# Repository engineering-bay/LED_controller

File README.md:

# LED_controller
Светодиодный драйвер

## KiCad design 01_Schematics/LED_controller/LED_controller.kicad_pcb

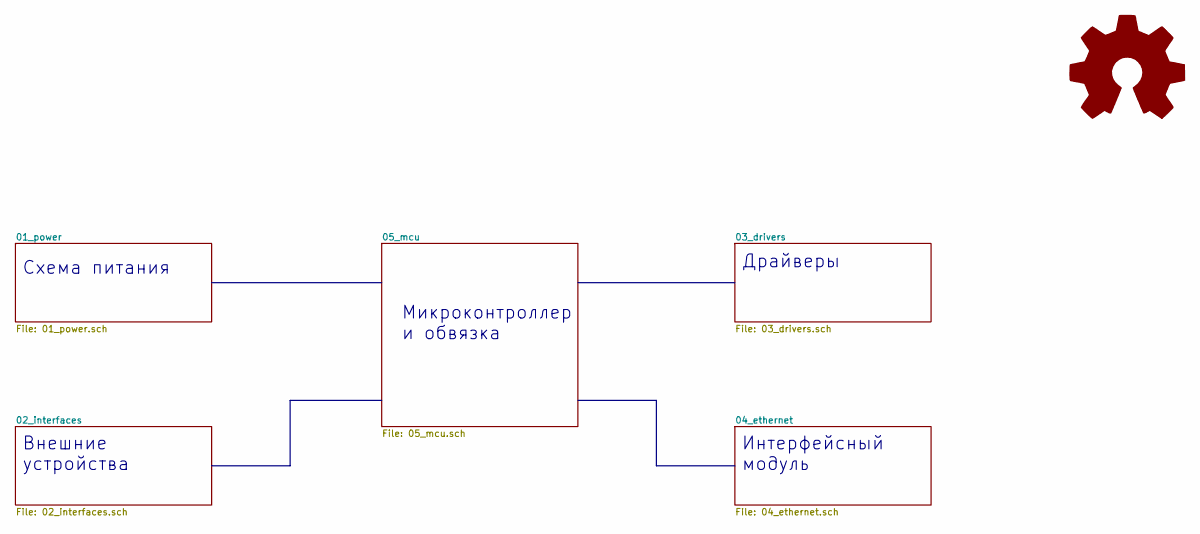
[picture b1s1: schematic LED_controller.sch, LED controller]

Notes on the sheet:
Схема питания
Микроконтроллер и обвязка
Внешние устройства
Интерфейсный модуль
Драйверы

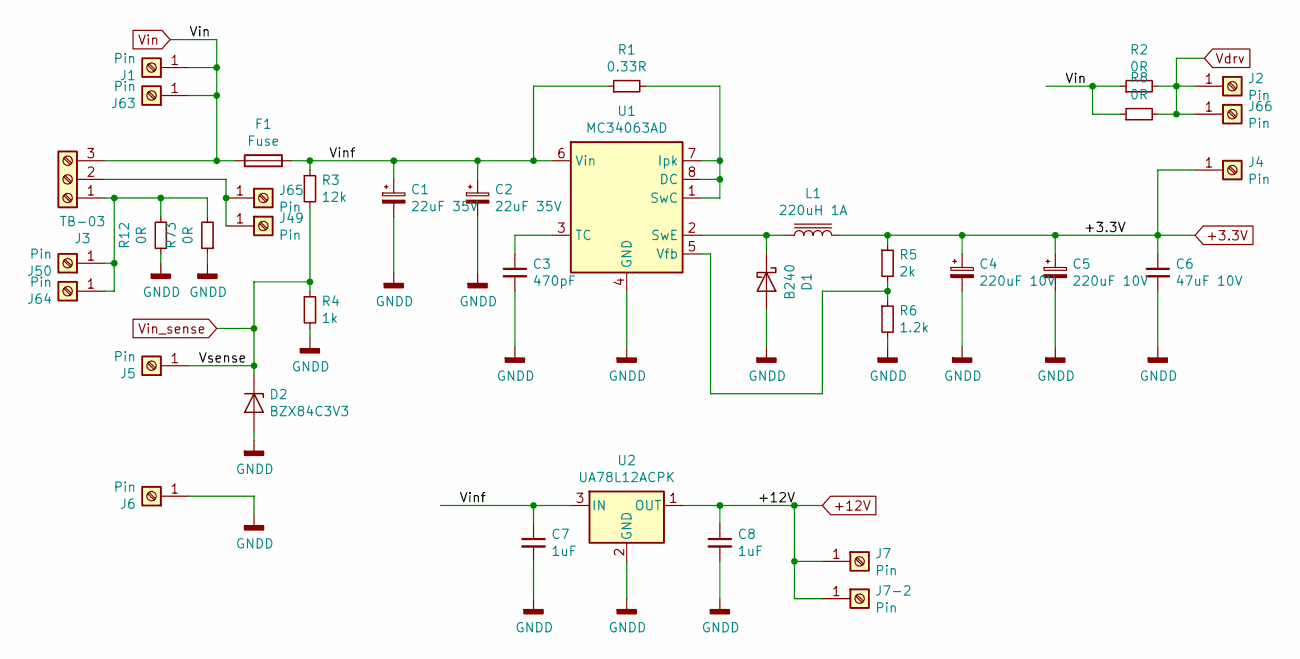
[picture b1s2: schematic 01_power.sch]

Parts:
C1, C2: 22uF 35V; CP_EIA-7343-31_Kemet-D_Pad2.25x2.55mm_HandSolder; partnum 293D226X9035D2TE3
C3: 470pF; C_0805_2012Metric_Pad1.15x1.40mm_HandSolder; partnum CC0805JRNPO9BN471
C4, C5: 220uF 10V; CP_EIA-7343-31_Kemet-D_Pad2.25x2.55mm_HandSolder; partnum 293D227X9010D2TE3
C6: 47uF 10V; C_1206_3216Metric_Pad1.42x1.75mm_HandSolder; partnum GRM31CR61A476ME15L
C7, C8: 1uF; C_0805_2012Metric_Pad1.15x1.40mm_HandSolder; partnum CC0805KKX7R9BB105
D1: B240; D_SMB
D2: BZX84C3V3; D_SOT-23_ANK
F1: Fuse; MF-R185; partnum MF-R090
J1, J2, J4, J5, J6, J7, J7-2, J49, J50, J63, J64, J65, J66: Pin; TestPoint_THTPad_2.0x2.0mm_Drill1.0mm
J3: TB-03; TB-03_metric; partnum TB-03
L1: 220uH 1A; SRR1208; partnum SRR1208-221KL
R1: 0.33R; R_0805_2012Metric_Pad1.15x1.40mm_HandSolder; partnum RL0805FR-070R33L
R2, R8, R12, R73: 0R; R_0805_2012Metric_Pad1.15x1.40mm_HandSolder; partnum RC2010JK-070RL
R3: 12k; R_0805_2012Metric_Pad1.15x1.40mm_HandSolder; partnum RC0805FR-0712KL
R4: 1k; R_0805_2012Metric_Pad1.15x1.40mm_HandSolder; partnum RC0805FR-071KL
R5: 2k; R_0805_2012Metric_Pad1.15x1.40mm_HandSolder; partnum RC0805FR-072KL
R6: 1.2k; R_0805_2012Metric_Pad1.15x1.40mm_HandSolder; partnum RC0805FR-071K2L
U1: MC34063AD; SOIC-8_3.9x4.9mm_P1.27mm
U2: UA78L12ACPK; SOT-89-3; partnum UA78L12ACPK

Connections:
+3.3V: C4.1, C5.1, C6.1, J4.1, L1.2, R5.1; also elsewhere on the board
+12V: C8.1, J7.1, J7-2.1, U2.1 (OUT); also elsewhere on the board
/01_power/Vinf: C1.1, C2.1, C7.1, F1.2, R1.1, R3.1, U1.6 (Vin), U2.3 (IN)
GND: C1.2, C2.2, C3.2, C4.2, C5.2, C6.2, C7.2, C8.2, D1.2 (A), D2.2 (A), J6.1, R4.2, R6.2, R12.1, R73.1, U1.4 (GND), U2.2 (GND); also elsewhere on the board
unnamed: C3.1, U1.3 (TC)
unnamed: D1.1 (K), L1.1, U1.2 (SwE)
unnamed: J3.1, J50.1, J64.1, R12.2, R73.2
unnamed: J3.2, J49.1, J65.1
unnamed: R1.2, U1.1 (SwC), U1.7 (Ipk), U1.8 (DC)
unnamed: R5.2, R6.1, U1.5 (Vfb)
Vdrv: J2.1, J66.1, R2.2, R8.2; also elsewhere on the board
Vin: F1.1, J1.1, J3.3, J63.1, R2.1, R8.1
Vin_sense: D2.1 (K), J5.1, R3.2, R4.1; also elsewhere on the board

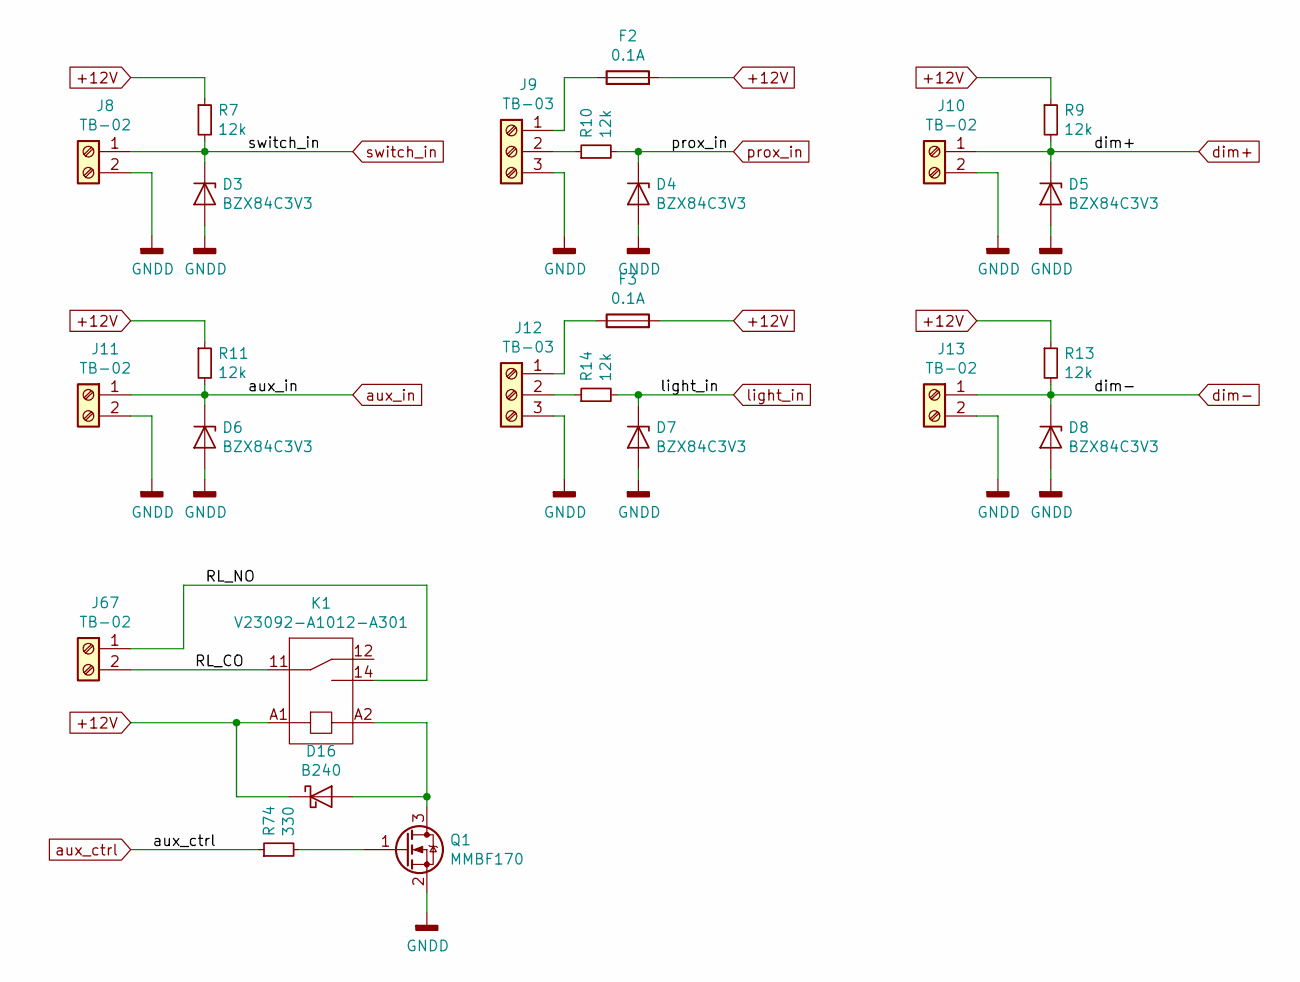
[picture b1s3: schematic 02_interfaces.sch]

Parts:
D3, D4, D5, D6, D7, D8: BZX84C3V3; D_SOT-23_ANK
D16: B240; D_SMB
F2, F3: 0.1A; R_1812_4532Metric_Pad1.30x3.40mm_HandSolder; partnum MF-MSMF010
J8, J10, J11, J13, J67: TB-02; TB-02_metric; partnum 300-021-12
J9, J12: TB-03; TB-03_metric; partnum 300-031-12
K1: V23092-A1012-A301; Relay_TE_V23092
Q1: MMBF170; SOT-23
R7, R9, R10, R11, R13, R14: 12k; R_0805_2012Metric_Pad1.15x1.40mm_HandSolder; partnum RC0805FR-0712KL
R74: 330; R_0805_2012Metric_Pad1.15x1.40mm_HandSolder; partnum RC0805FR-07330RL

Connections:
+12V: D16.1 (K), F2.2, F3.2, K1.A1, R7.1, R9.1, R11.1, R13.1; also elsewhere on the board
/02_interfaces/RL_CO: J67.2, K1.11
/02_interfaces/RL_NO: J67.1, K1.14
GND: D3.2 (A), D4.2 (A), D5.2 (A), D6.2 (A), D7.2 (A), D8.2 (A), J8.2, J9.3, J10.2, J11.2, J12.3, J13.2, Q1.2 (S); also elsewhere on the board
unnamed: D16.2 (A), K1.A2, Q1.3 (D)
unnamed: F2.1, J9.1
unnamed: F3.1, J12.1
unnamed: J9.2, R10.1
unnamed: J12.2, R14.1
unnamed: Q1.1 (G), R74.2
aux_ctrl: R74.1; also elsewhere on the board
aux_in: D6.1 (K), J11.1, R11.2; also elsewhere on the board
dim+: D5.1 (K), J10.1, R9.2; also elsewhere on the board
dim-: D8.1 (K), J13.1, R13.2; also elsewhere on the board
light_in: D7.1 (K), R14.2; also elsewhere on the board
prox_in: D4.1 (K), R10.2; also elsewhere on the board
switch_in: D3.1 (K), J8.1, R7.2; also elsewhere on the board

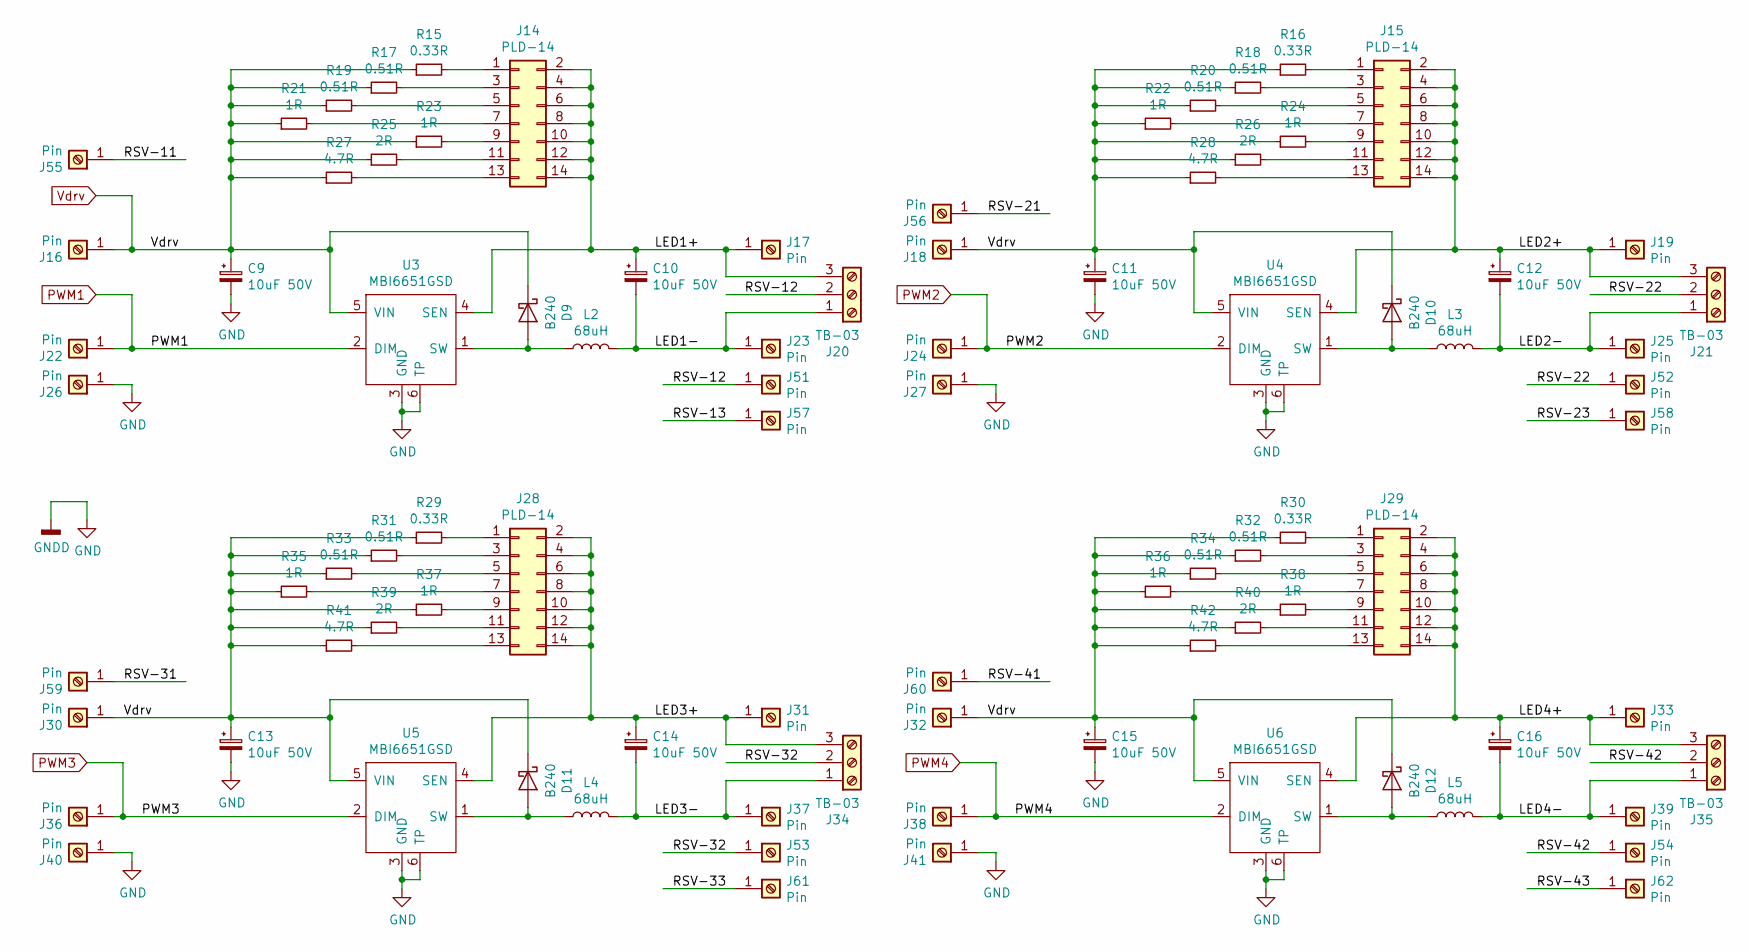
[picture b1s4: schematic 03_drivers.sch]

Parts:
C9, C10, C11, C12, C13, C14, C15, C16: 10uF 50V; CP_EIA-7343-31_Kemet-D_Pad2.25x2.55mm_HandSolder; partnum 293D106X9035D2TE3
D9, D10, D11, D12: B240; D_SMB
J14, J15, J28, J29: PLD-14; PinHeader_2x07_P2.54mm_Vertical; partnum PLD-14
J16, J17, J18, J19, J22, J23, J24, J25, J26, J27, J30, J31, J32, J33, J36, J37, J38, J39, J40, J41, J51, J52, J53, J54, J55, J56, J57, J58, J59, J60, J61, J62: Pin; TestPoint_THTPad_2.0x2.0mm_Drill1.0mm
J20, J21, J34, J35: TB-03; TB-03_metric; partnum TB-03
L2, L3, L4, L5: 68uH; L_Bourns-SRR1005
R15, R16, R29, R30: 0.33R; R_0805_2012Metric_Pad1.15x1.40mm_HandSolder; partnum RL0805FR-070R33L
R17, R18, R19, R20, R31, R32, R33, R34: 0.51R; R_0805_2012Metric_Pad1.15x1.40mm_HandSolder; partnum RL0805FR-070R51L
R21, R22, R23, R24, R35, R36, R37, R38: 1R; R_0805_2012Metric_Pad1.15x1.40mm_HandSolder; partnum RC0805FR-071RL
R25, R26, R39, R40: 2R; R_0805_2012Metric_Pad1.15x1.40mm_HandSolder; partnum RC0805FR-072RL
R27, R28, R41, R42: 4.7R; R_0805_2012Metric_Pad1.15x1.40mm_HandSolder; partnum RC0805FR-074R7L
U3, U4, U5, U6: MBI6651GSD; TO-252-5L; partnum MBI6651GSD-A

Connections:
/03_drivers/LED1+: C10.1, J14.2, J14.4, J14.6, J14.8, J14.10, J14.12, J14.14, J17.1, J20.3, U3.4 (SEN)
/03_drivers/LED1-: C10.2, J20.1, J23.1, L2.2
/03_drivers/LED2+: C12.1, J15.2, J15.4, J15.6, J15.8, J15.10, J15.12, J15.14, J19.1, J21.3, U4.4 (SEN)
/03_drivers/LED2-: C12.2, J21.1, J25.1, L3.2
/03_drivers/LED3+: C14.1, J28.2, J28.4, J28.6, J28.8, J28.10, J28.12, J28.14, J31.1, J34.3, U5.4 (SEN)
/03_drivers/LED3-: C14.2, J34.1, J37.1, L4.2
/03_drivers/LED4+: C16.1, J29.2, J29.4, J29.6, J29.8, J29.10, J29.12, J29.14, J33.1, J35.3, U6.4 (SEN)
/03_drivers/LED4-: C16.2, J35.1, J39.1, L5.2
/03_drivers/RSV-11: J55.1
/03_drivers/RSV-12: J20.2, J51.1
/03_drivers/RSV-13: J57.1
/03_drivers/RSV-21: J56.1
/03_drivers/RSV-22: J21.2, J52.1
/03_drivers/RSV-23: J58.1
/03_drivers/RSV-31: J59.1
/03_drivers/RSV-32: J34.2, J53.1
/03_drivers/RSV-33: J61.1
/03_drivers/RSV-41: J60.1
/03_drivers/RSV-42: J35.2, J54.1
/03_drivers/RSV-43: J62.1
GND: C9.2, C11.2, C13.2, C15.2, J26.1, J27.1, J40.1, J41.1, U3.3 (GND), U3.6 (TP), U4.3 (GND), U4.6 (TP), U5.3 (GND), U5.6 (TP), U6.3 (GND), U6.6 (TP); also elsewhere on the board
unnamed: D9.2 (A), L2.1, U3.1 (SW)
unnamed: D10.2 (A), L3.1, U4.1 (SW)
unnamed: D11.2 (A), L4.1, U5.1 (SW)
unnamed: D12.2 (A), L5.1, U6.1 (SW)
unnamed: J14.1, R15.2
unnamed: J14.3, R17.2
unnamed: J14.5, R19.2
unnamed: J14.7, R21.2
unnamed: J14.9, R23.2
unnamed: J14.11, R25.2
unnamed: J14.13, R27.2
unnamed: J15.1, R16.2
unnamed: J15.3, R18.2
unnamed: J15.5, R20.2
unnamed: J15.7, R22.2
unnamed: J15.9, R24.2
unnamed: J15.11, R26.2
unnamed: J15.13, R28.2
unnamed: J28.1, R29.2
unnamed: J28.3, R31.2
unnamed: J28.5, R33.2
unnamed: J28.7, R35.2
unnamed: J28.9, R37.2
unnamed: J28.11, R39.2
unnamed: J28.13, R41.2
unnamed: J29.1, R30.2
unnamed: J29.3, R32.2
unnamed: J29.5, R34.2
unnamed: J29.7, R36.2
unnamed: J29.9, R38.2
unnamed: J29.11, R40.2
unnamed: J29.13, R42.2
PWM1: J22.1, U3.2 (DIM); also elsewhere on the board
PWM2: J24.1, U4.2 (DIM); also elsewhere on the board
PWM3: J36.1, U5.2 (DIM); also elsewhere on the board
PWM4: J38.1, U6.2 (DIM); also elsewhere on the board
Vdrv: C9.1, C11.1, C13.1, C15.1, D9.1 (K), D10.1 (K), D11.1 (K), D12.1 (K), J16.1, J18.1, J30.1, J32.1, R15.1, R16.1, R17.1, R18.1, R19.1, R20.1, R21.1, R22.1, R23.1, R24.1, R25.1, R26.1, R27.1, R28.1, R29.1, R30.1, R31.1, R32.1, R33.1, R34.1, R35.1, R36.1, R37.1, R38.1, R39.1, R40.1, R41.1, R42.1, U3.5 (VIN), U4.5 (VIN), U5.5 (VIN), U6.5 (VIN); also elsewhere on the board

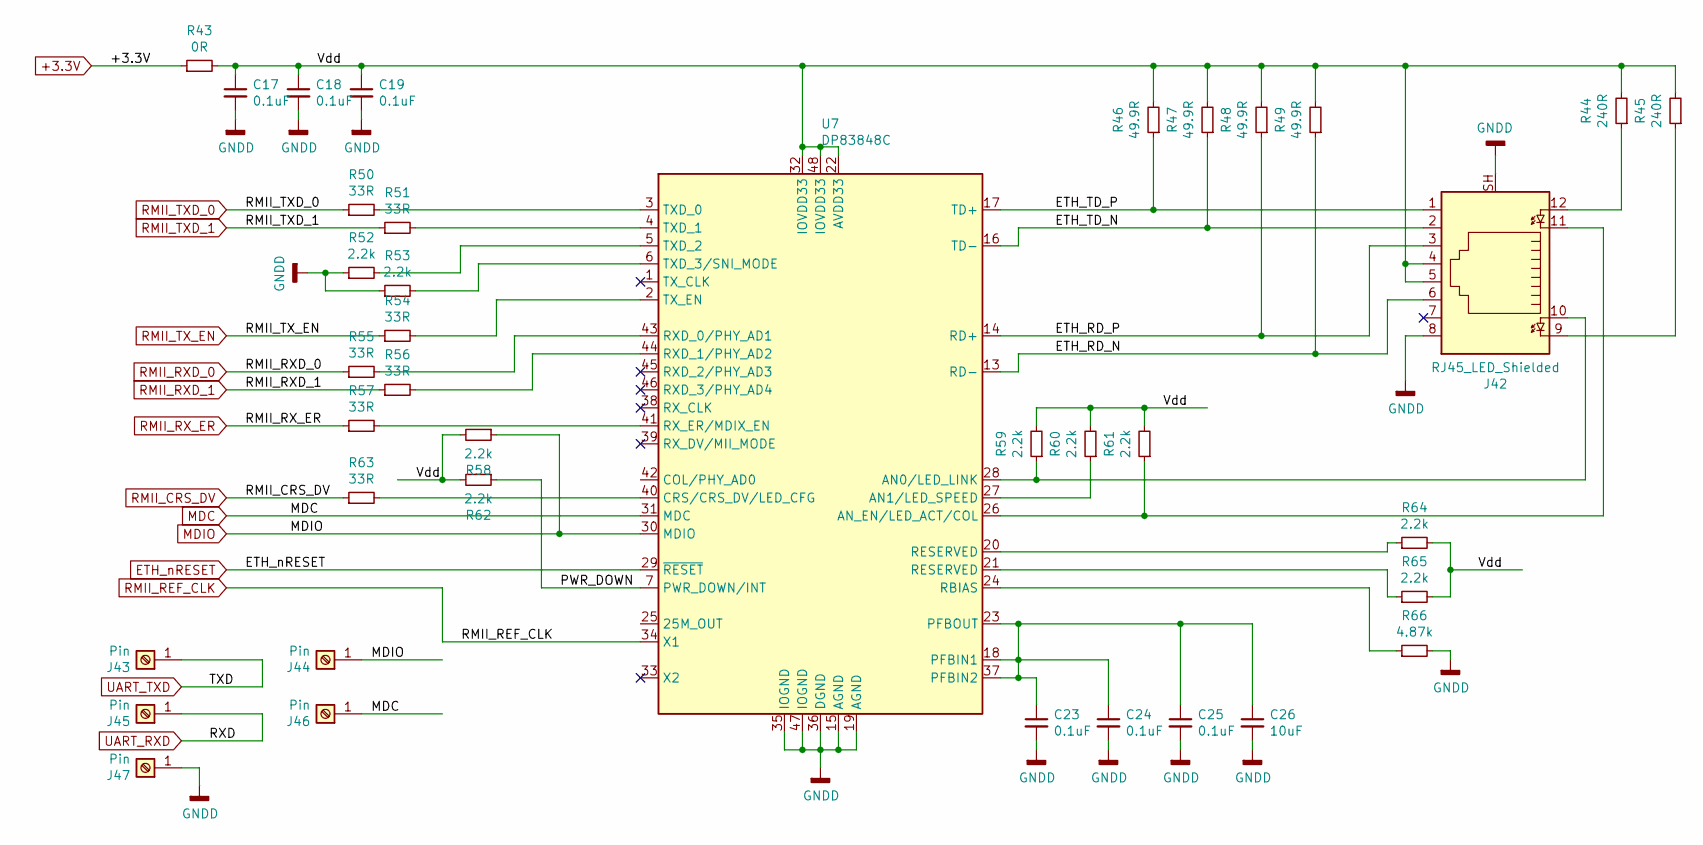
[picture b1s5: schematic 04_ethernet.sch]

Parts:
C17, C18, C19, C23, C24, C25: 0.1uF; C_0805_2012Metric_Pad1.15x1.40mm_HandSolder; partnum CC0805JRX7R9BB104
C26: 10uF; C_0805_2012Metric_Pad1.15x1.40mm_HandSolder; partnum GRM21BR61C106KE15L
J42: RJ45_LED_Shielded; Hanrun_HR9111105A; partnum HR911105A
J43, J44, J45, J46, J47: Pin; TestPoint_THTPad_2.0x2.0mm_Drill1.0mm
R43: 0R; R_0805_2012Metric_Pad1.15x1.40mm_HandSolder; partnum RC2010JK-070RL
R44, R45: 240R; R_0805_2012Metric_Pad1.15x1.40mm_HandSolder; partnum RC0805FR-07240RL
R46, R47, R48, R49: 49.9R; R_0805_2012Metric_Pad1.15x1.40mm_HandSolder; partnum RC0805FR-0749R9L
R50, R51, R54, R55, R56, R57, R63: 33R; R_0805_2012Metric_Pad1.15x1.40mm_HandSolder; partnum RC0805FR-0733RL
R52, R53, R58, R59, R60, R61, R62, R64, R65: 2.2k; R_0805_2012Metric_Pad1.15x1.40mm_HandSolder; partnum RC0805FR-072K2L
R66: 4.87k; R_0805_2012Metric_Pad1.15x1.40mm_HandSolder; partnum RC0805FR-074K87L
U7: DP83848C; LQFP-48_7x7mm_P0.5mm

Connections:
+3.3V: R43.1; also elsewhere on the board
/04_ethernet/ETH_RD_N: J42.6, R49.1, U7.13 (RD-)
/04_ethernet/ETH_RD_P: J42.3, R48.1, U7.14 (RD+)
/04_ethernet/ETH_TD_N: J42.2, R47.1, U7.16 (TD-)
/04_ethernet/ETH_TD_P: J42.1, R46.1, U7.17 (TD+)
/04_ethernet/PWR_DOWN: R62.1, U7.7 (PWR_DOWN/INT)
/04_ethernet/Vdd: C17.1, C18.1, C19.1, J42.4, J42.5, R43.2, R44.2, R45.2, R46.2, R47.2, R48.2, R49.2, R58.2, R59.2, R60.2, R61.2, R62.2, R64.2, R65.2, U7.22 (AVDD33), U7.32 (IOVDD33), U7.48 (IOVDD33)
ETH_nRESET: U7.29 (~RESET~); also elsewhere on the board
GND: C17.2, C18.2, C19.2, C23.2, C24.2, C25.2, C26.2, J42.8, J42.SH, J47.1, R52.1, R53.1, R66.2, U7.15 (AGND), U7.19 (AGND), U7.35 (IOGND), U7.36 (DGND), U7.47 (IOGND); also elsewhere on the board
MDC: J46.1, U7.31 (MDC); also elsewhere on the board
MDIO: J44.1, R58.1, U7.30 (MDIO); also elsewhere on the board
unnamed: C23.1, C24.1, C25.1, C26.1, U7.18 (PFBIN1), U7.23 (PFBOUT), U7.37 (PFBIN2)
unnamed: J42.9, R45.1
unnamed: J42.10, R59.1, U7.28 (AN0/LED_LINK)
unnamed: J42.11, R61.1, U7.26 (AN_EN/LED_ACT/COL)
unnamed: J42.12, R44.1
unnamed: R50.2, U7.3 (TXD_0)
unnamed: R51.2, U7.4 (TXD_1)
unnamed: R52.2, U7.5 (TXD_2)
unnamed: R53.2, U7.6 (TXD_3/SNI_MODE)
unnamed: R54.2, U7.2 (TX_EN)
unnamed: R55.2, U7.43 (RXD_0/PHY_AD1)
unnamed: R56.2, U7.44 (RXD_1/PHY_AD2)
unnamed: R57.2, U7.41 (RX_ER/MDIX_EN)
unnamed: R60.1, U7.27 (AN1/LED_SPEED)
unnamed: R63.2, U7.40 (CRS/CRS_DV/LED_CFG)
unnamed: R64.1, U7.20 (RESERVED)
unnamed: R65.1, U7.21 (RESERVED)
unnamed: R66.1, U7.24 (RBIAS)
RMII_CRS_DV: R63.1; also elsewhere on the board
RMII_REF_CLK: U7.34 (X1); also elsewhere on the board
RMII_RXD_0: R55.1; also elsewhere on the board
RMII_RXD_1: R56.1; also elsewhere on the board
RMII_RX_ER: R57.1; also elsewhere on the board
RMII_TXD_0: R50.1; also elsewhere on the board
RMII_TXD_1: R51.1; also elsewhere on the board
RMII_TX_EN: R54.1; also elsewhere on the board
UART_RXD: J45.1; also elsewhere on the board
UART_TXD: J43.1; also elsewhere on the board

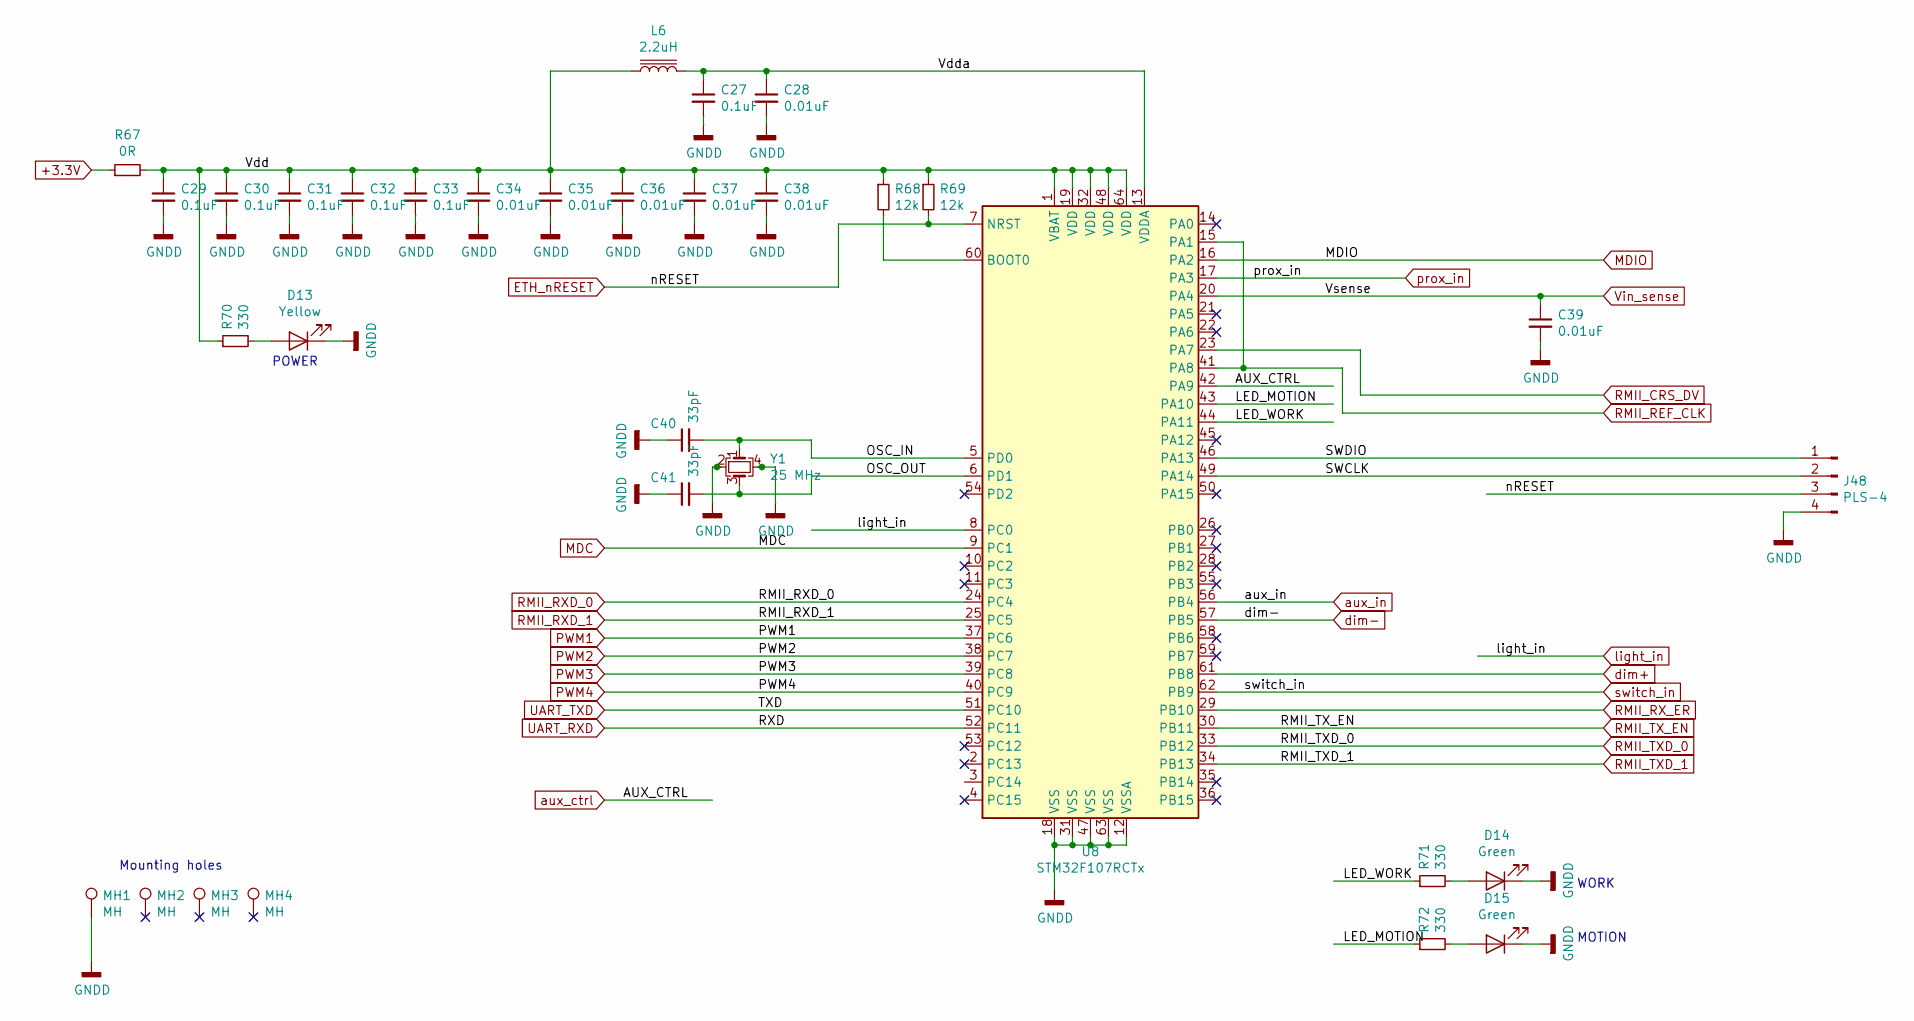
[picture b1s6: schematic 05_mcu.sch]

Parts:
C27, C29, C30, C31, C32, C33: 0.1uF; C_0805_2012Metric_Pad1.15x1.40mm_HandSolder; partnum CC0805JRX7R9BB104
C28, C34, C35, C36, C37, C38, C39: 0.01uF; C_0805_2012Metric_Pad1.15x1.40mm_HandSolder; partnum CC0805JRNPO9BN103
C40, C41: 33pF; C_0805_2012Metric_Pad1.15x1.40mm_HandSolder; partnum CC0805JRNPO9BN330
D13: Yellow; LED_0805_2012Metric_HandSolder; partnum TO-2013BC-MYF
D14, D15: Green; LED_0805_2012Metric_HandSolder; partnum TO-2013BC-PG
J48: PLS-4; PinHeader_1x04_P2.54mm_Vertical; partnum PLS-4
L6: 2.2uH; L_0805_2012Metric_Pad1.15x1.40mm_HandSolder; partnum B82498F1222J000
MH1, MH2, MH3, MH4: MH; MountingHole_3.2mm_M3_Pad_Via
R67: 0R; R_0805_2012Metric_Pad1.15x1.40mm_HandSolder; partnum RC2010JK-070RL
R68, R69: 12k; R_0805_2012Metric_Pad1.15x1.40mm_HandSolder; partnum RC0805FR-0712KL
R70, R71, R72: 330; R_0805_2012Metric_Pad1.15x1.40mm_HandSolder; partnum RC0805FR-07330RL
U8: STM32F107RCTx; LQFP-64_10x10mm_P0.5mm; partnum STM32F107RCTx
Y1: 25 MHz; Crystal_SMD_3225-4Pin_3.2x2.5mm_HandSoldering; partnum KX-7 25.0 MHz

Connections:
+3.3V: R67.1; also elsewhere on the board
/05_mcu/LED_MOTION: R72.1, U8.43 (PA10)
/05_mcu/LED_WORK: R71.1, U8.44 (PA11)
/05_mcu/OSC_IN: C40.2, U8.5 (PD0), Y1.1
/05_mcu/OSC_OUT: C41.2, U8.6 (PD1), Y1.3
/05_mcu/SWCLK: J48.2, U8.49 (PA14)
/05_mcu/SWDIO: J48.1, U8.46 (PA13)
/05_mcu/Vdd: C29.1, C30.1, C31.1, C32.1, C33.1, C34.1, C35.1, C36.1, C37.1, C38.1, L6.1, R67.2, R68.1, R69.1, R70.1, U8.1 (VBAT), U8.19 (VDD), U8.32 (VDD), U8.48 (VDD), U8.64 (VDD)
/05_mcu/Vdda: C27.1, C28.1, L6.2, U8.13 (VDDA)
ETH_nRESET: J48.3, R69.2, U8.7 (NRST); also elsewhere on the board
GND: C27.2, C28.2, C29.2, C30.2, C31.2, C32.2, C33.2, C34.2, C35.2, C36.2, C37.2, C38.2, C39.2, C40.1, C41.1, D13.1 (K), D14.1 (K), D15.1 (K), J48.4, MH1.1, U8.12 (VSSA), U8.18 (VSS), U8.31 (VSS), U8.47 (VSS), U8.63 (VSS), Y1.2, Y1.4; also elsewhere on the board
MDC: U8.9 (PC1); also elsewhere on the board
MDIO: U8.16 (PA2); also elsewhere on the board
unnamed: D13.2 (A), R70.2
unnamed: D14.2 (A), R71.2
unnamed: D15.2 (A), R72.2
unnamed: R68.2, U8.60 (BOOT0)
PWM1: U8.37 (PC6); also elsewhere on the board
PWM2: U8.38 (PC7); also elsewhere on the board
PWM3: U8.39 (PC8); also elsewhere on the board
PWM4: U8.40 (PC9); also elsewhere on the board
RMII_CRS_DV: U8.23 (PA7); also elsewhere on the board
RMII_REF_CLK: U8.15 (PA1), U8.41 (PA8); also elsewhere on the board
RMII_RXD_0: U8.24 (PC4); also elsewhere on the board
RMII_RXD_1: U8.25 (PC5); also elsewhere on the board
RMII_RX_ER: U8.29 (PB10); also elsewhere on the board
RMII_TXD_0: U8.33 (PB12); also elsewhere on the board
RMII_TXD_1: U8.34 (PB13); also elsewhere on the board
RMII_TX_EN: U8.30 (PB11); also elsewhere on the board
UART_RXD: U8.52 (PC11); also elsewhere on the board
UART_TXD: U8.51 (PC10); also elsewhere on the board
Vin_sense: C39.1, U8.20 (PA4); also elsewhere on the board
aux_ctrl: U8.42 (PA9); also elsewhere on the board
aux_in: U8.56 (PB4); also elsewhere on the board
dim+: U8.61 (PB8); also elsewhere on the board
dim-: U8.57 (PB5); also elsewhere on the board
light_in: U8.8 (PC0); also elsewhere on the board
prox_in: U8.17 (PA3); also elsewhere on the board
switch_in: U8.62 (PB9); also elsewhere on the board

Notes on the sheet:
POWER
WORK
MOTION
Mounting holes

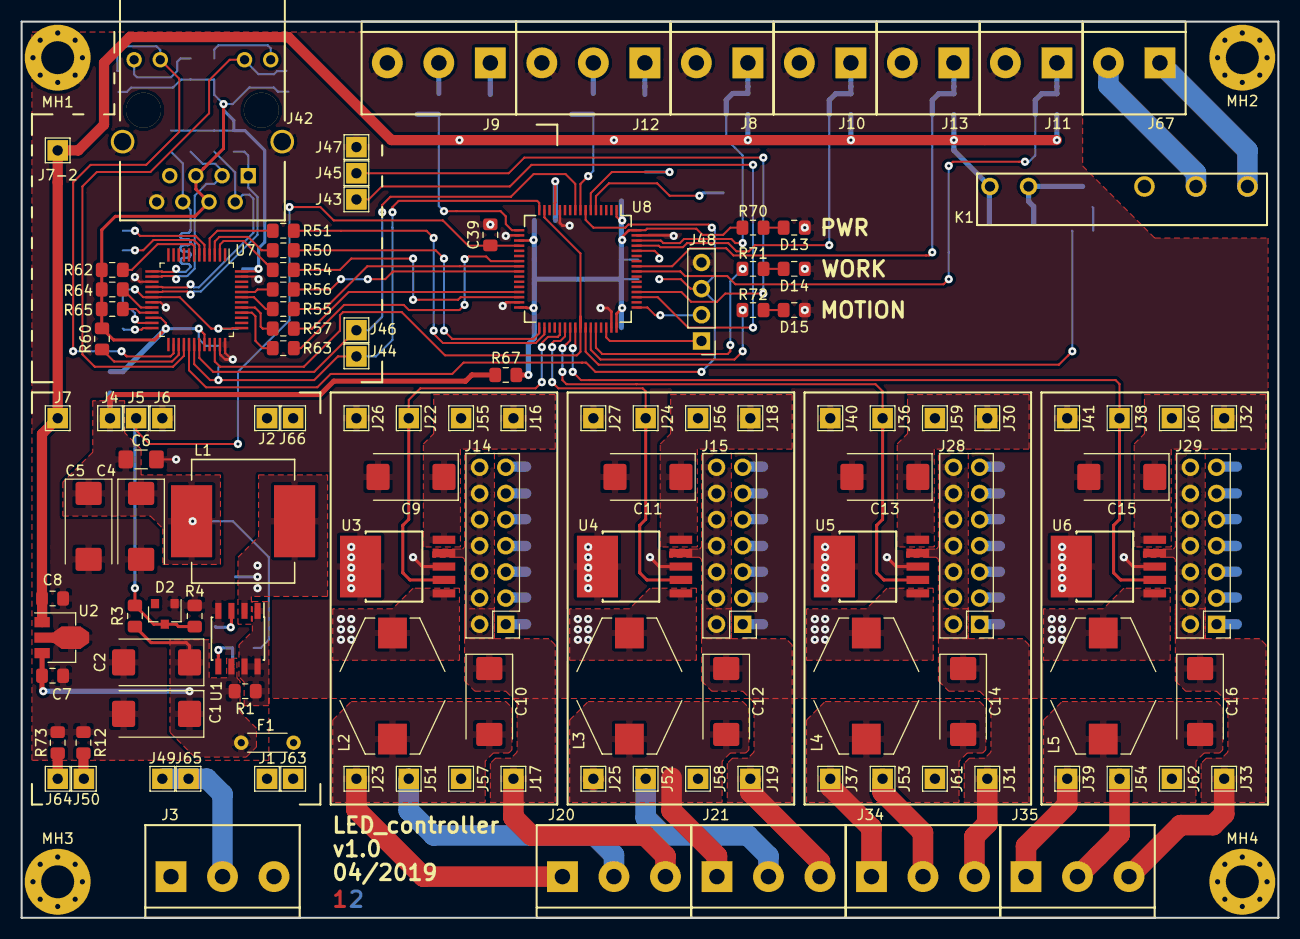
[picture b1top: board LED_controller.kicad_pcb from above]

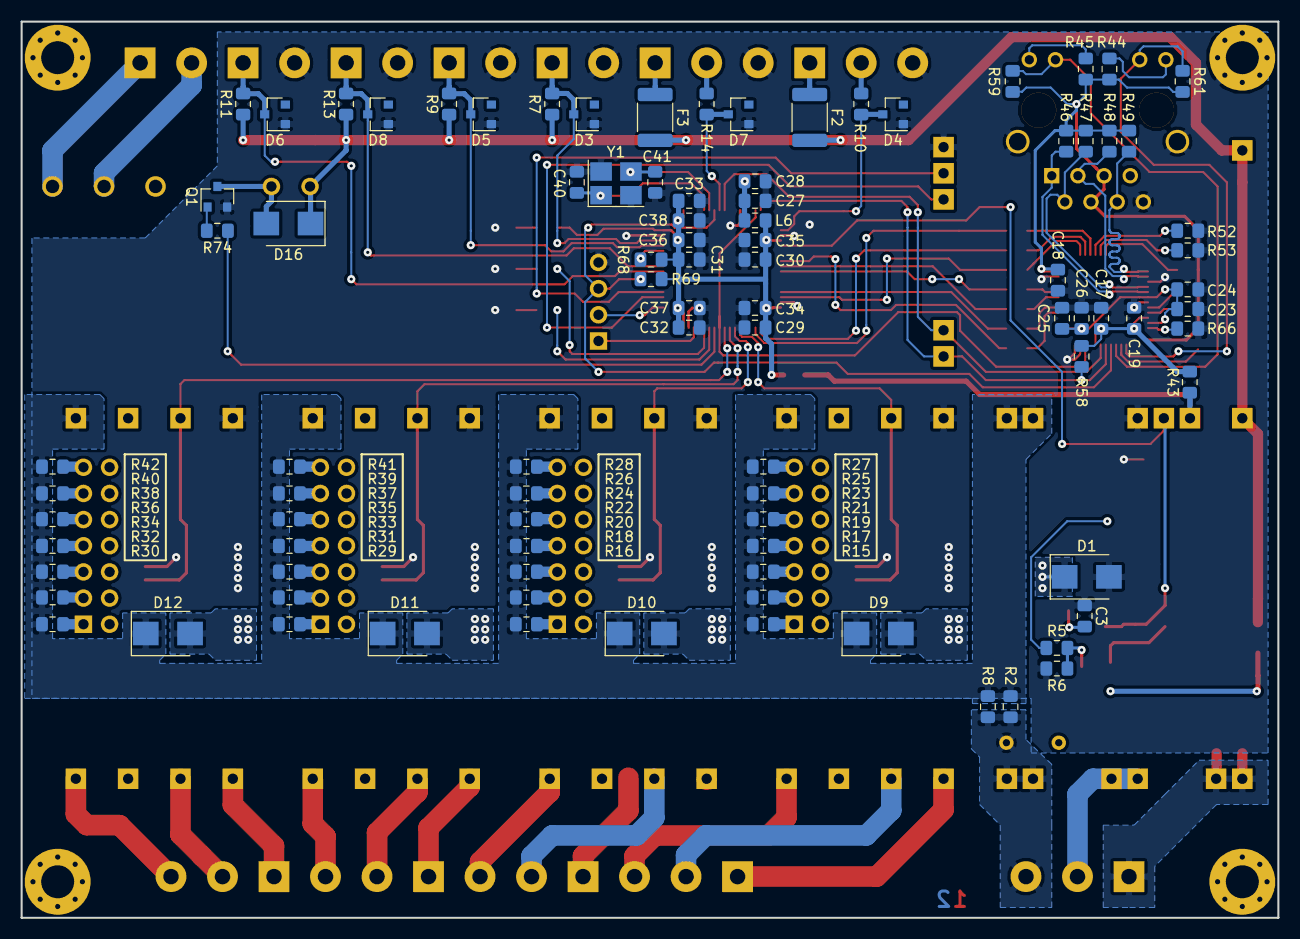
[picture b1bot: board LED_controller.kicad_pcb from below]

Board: 2 copper layers, 122.0 x 87.0 mm, 220 parts (93 on the bottom side), 125 nets.

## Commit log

2018-12-20 Добавлено: - Схема электрическая; - Библиотека extras (всё, чего не было в стандартных библиотеках); - даташиты на компоненты.
2019-04-28 - Добавлена печатная плата; - Добавлены файлы посадочных мест использованных компонентов и STEP модели; - Добавлены файлы механической сборки (Solidworks);
2019-07-31 - Исправлена ошибка с неправильным подключением цепи обратной связи микросхемы U1; - Плата переразведена с учетом изменений в схеме; - Добавлен файл BOM;
